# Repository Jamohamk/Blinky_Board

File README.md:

# Blinky_Board
A Board that blinks
BOM: Since this is a kit project i dont need to do a very long BOM 
Photos of Blinky Board:
SCHEMATIC: 
PCB: 
WHY:
So ive only used kicad once before this and i want to be able to build pcb's so i thought this would be helpful. And ive never worked with LEDs so i think that is exciting.
QUICK NOTE FOR PERSON CREATING THIS:
1. so the files that end with sch and pcb DO NOT USE those are deprecated
2. BackPlate_BlinkyBoard is the plate that i want the parts for the PCB on KIcad ignored it for some reason when exporting so i recreated it in fusion ill also include a screenshot for reference
3. BlinkyBoard.step is the right step file but instead of having the spotify logo as the background it has a square. :/

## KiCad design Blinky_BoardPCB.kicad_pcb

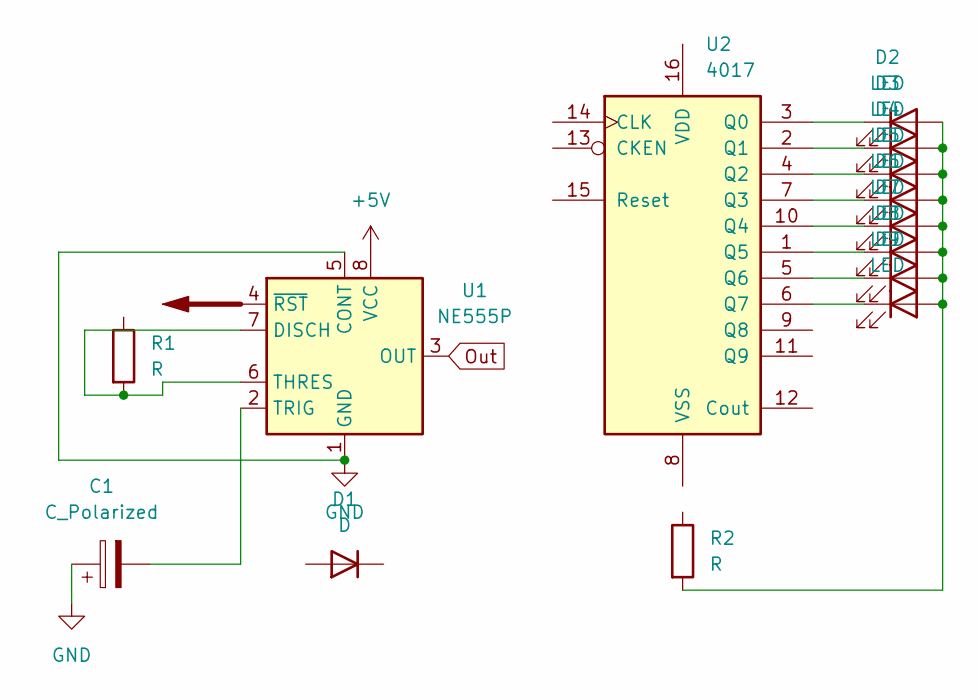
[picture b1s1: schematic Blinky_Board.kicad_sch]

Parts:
C1: C_Polarized; CP_Radial_D5.0mm_P2.00mm
D1: D; C_Disc_D7.5mm_W2.5mm_P5.00mm
D2, D3, D4, D5, D6, D7, D8, D9: LED; LED_D3.0mm
R1, R2: R; R_Axial_DIN0207_L6.3mm_D2.5mm_P7.62mm_Horizontal
U1: NE555P; DIP-8_W7.62mm
U2: 4017; DIP-16_W7.62mm

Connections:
+5V: U1.8 (VCC)
GND: C1.1, U1.1 (GND), U1.5 (CONT)
unnamed: D2.2 (A), D3.2 (A), D4.2 (A), D5.2 (A), D6.2 (A), D7.2 (A), D8.2 (A), D9.2 (A), R2.2
unnamed: D2.1 (K), U2.3 (Q0)
unnamed: D3.1 (K), U2.2 (Q1)
unnamed: D4.1 (K), U2.4 (Q2)
unnamed: D5.1 (K), U2.7 (Q3)
unnamed: D6.1 (K), U2.10 (Q4)
unnamed: D7.1 (K), U2.1 (Q5)
unnamed: D8.1 (K), U2.5 (Q6)
unnamed: D9.1 (K), U2.6 (Q7)
unnamed: R1.2, U1.6 (THRES), U1.7 (DISCH)
unnamed: C1.2, U1.2 (TRIG)
Out: U1.3 (OUT)

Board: 2 copper layers, 14 parts (0 on the bottom side), 12 nets, no tracks yet.

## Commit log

2026-05-09 Update README with BOM and images
    Added BOM note and images of PCB and schematic.
2026-05-10 Swap PCB and SCHEMATIC image sections in README
2026-05-10 Add quick notes for project creator
    Added notes for the person creating the project, including file usage and issues with the PCB design.
2026-05-11 Enhance README with project motivation
    Added a 'WHY' section to explain the motivation behind the project.
